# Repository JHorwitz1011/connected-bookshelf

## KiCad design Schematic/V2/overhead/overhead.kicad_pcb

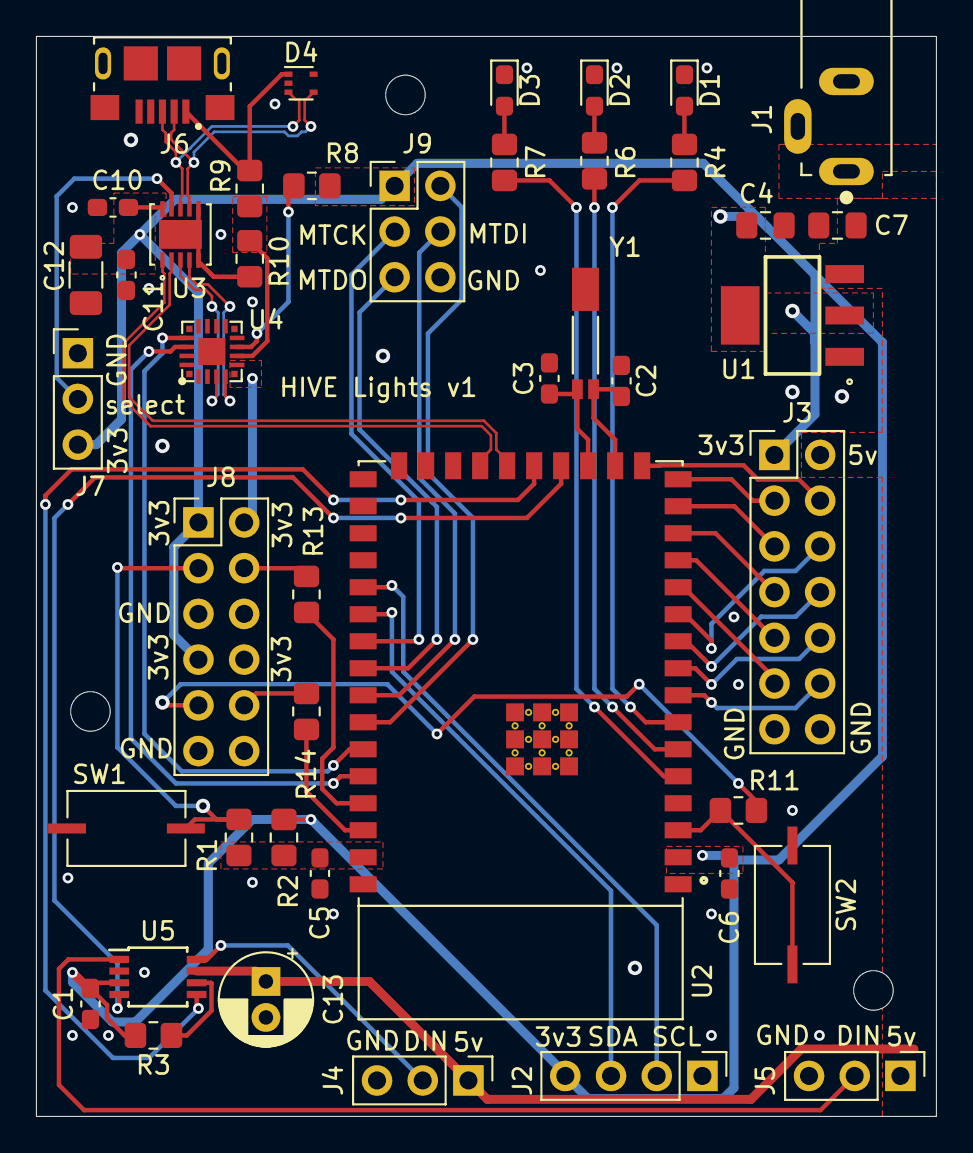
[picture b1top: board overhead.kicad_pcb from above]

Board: 2 copper layers, 50.0 x 60.0 mm, 44 parts (0 on the bottom side), 52 nets.

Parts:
C1, C6: 2.2 uF; C_0603_1608Metric_Pad1.08x0.95mm_HandSolder
C2, C3: 7 pF; C_0603_1608Metric_Pad1.08x0.95mm_HandSolder
C4, C7: 10 uF; C_0805_2012Metric_Pad1.18x1.45mm_HandSolder
C5: 0.1uF; C_0603_1608Metric_Pad1.08x0.95mm_HandSolder
C10, C11: 0.1 uF; C_0603_1608Metric_Pad1.08x0.95mm_HandSolder
C12: 4.7 uF; C_1206_3216Metric_Pad1.33x1.80mm_HandSolder
C13: 100 uF; CP_Radial_D5.0mm_P2.00mm
D1, D2, D3: LED; LED_0603_1608Metric_Pad1.05x0.95mm_HandSolder
D4: SP0503BAHTG; SOT-553
J1: PJ-031C; CUI_PJ-031C
J2: I2C; PinHeader_1x04_P2.54mm_Vertical
J3: GPIO; PinHeader_2x07_P2.54mm_Vertical
J4: Neopixel 1; PinHeader_1x03_P2.54mm_Vertical
J5: Neopixel 2; PinHeader_1x03_P2.54mm_Vertical
J6: 10118193-0001LF; FCI_10118193-0001LF
J7: Select Jumper; PinHeader_1x03_P2.54mm_Vertical
J8: STRAPPING; PinHeader_2x06_P2.54mm_Vertical
J9: JTAG; PinHeader_2x03_P2.54mm_Vertical
R1, R11, R13, R14: 470; R_0805_2012Metric_Pad1.20x1.40mm_HandSolder
R2, R3, R8: 10k; R_0805_2012Metric_Pad1.20x1.40mm_HandSolder
R4: 70; R_0805_2012Metric_Pad1.20x1.40mm_HandSolder
R6, R7: 65; R_0805_2012Metric_Pad1.20x1.40mm_HandSolder
R9: 22.1k; R_0805_2012Metric_Pad1.20x1.40mm_HandSolder
R10: 47.5k; R_0805_2012Metric_Pad1.20x1.40mm_HandSolder
SW1, SW2: SW_DIP_x01; PTS636 SM25F SMTR LFS
U1: NCP1117ST33T3G; SOT230P700X180-4N
U2: ESP32-S2-WROOM; XCVR_ESP32-S2-WROOM
U3: PI3USB221EZWEX
U4: CP2102N-A02-GQFN20R
U5: NTB0102; TSSOP-8_3x3mm_P0.65mm
Y1: MS3V-T1R; XTAL_MS3V-T1R

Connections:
+3V3: C1.1, C4.1, C6.2, C10.1, C11.1, C12.1, J2.4, J3.1, J7.3, J8.1, J8.2, J8.7, J8.8, J9.1, R2.1, R3.2, R8.1, U1.2, U1.4, U2.2, U3.10, U4.6, U4.7, U5.3
+5V: C7.2, C13.1, J1.1, J3.2, J4.1, J5.1, U1.3, U5.7
/RSTB: R8.2, U4.9
/VSens: R9.2, R10.1, U4.8
/XTAL_N: C3.1, U2.19, Y1.1
/XTAL_P: C2.1, U2.18, Y1.2
/select: J7.2, U3.9
BOOT: R11.1, SW2.1, U2.3
CHIP_PU: J8.3, R1.1, SW1.1
DIN1: J4.2, U5.8
DIN2: J5.2, U5.1
ESP32)D+: U2.23, U3.1
ESP32)D-: U2.22, U3.2
GLED: R6.1, U2.6
GND: C1.2, C2.2, C3.2, C4.2, C5.2, C6.1, C7.1, C10.2, C11.2, C12.2, C13.2, D1.1, D2.1, D3.1, D4.2, J1.2, J1.3, J2.1, J3.13, J3.14, J4.3, J5.3, J6.5, J6.S1, J6.S2, J6.S3, J6.S4, J6.S5, J6.S6, J7.1, J8.5, J8.6, J8.11, J8.12, J9.6, R10.2, SW1.2, SW2.2, U1.1, U2.1, U2.26, U2.42, U2.43, U3.5, U3.6, U3.11, U4.3, U4.12, U4.21, U5.2
IO5: J3.12, U2.8
IO6: J3.10, U2.9
IO7: J3.8, U2.10
IO8: J3.6, U2.11
IO9: J3.11, U2.12
IO10: J3.9, U2.13
IO11: J3.7, U2.14
IO12: J3.5, U2.15
IO13: J3.3, U2.16
IO14: J3.4, U2.17
IO37-SCL: J2.2, U2.31
IO38-SDA: J2.3, U2.32
IO45: R13.1, U2.39
IO46: R14.1, U2.40
MTCK: J9.3, U2.33
MTDI: J9.4, U2.35
MTDO: J9.5, U2.34
MTMS: J9.2, U2.36
Neopixel1: U2.21, U5.5
Neopixel2: U2.20, U5.4
unnamed: C5.1, R1.2, R2.2, U2.41
unnamed: D1.2, R4.2
unnamed: D2.2, R6.2
unnamed: D3.2, R7.2
unnamed: J8.4, R13.2
unnamed: J8.9, R11.2
unnamed: J8.10, R14.2
unnamed: R3.1, U5.6
RLED: R4.1, U2.7
RX0: U2.37, U4.17
TX0: U2.38, U4.18
UART)D+: U3.3, U4.4
UART)D-: U3.4, U4.5
USB)D+: D4.3, J6.3, U3.8
USB)D-: D4.4, J6.2, U3.7
VBUS: D4.1, J6.1, R9.1
YLED: R7.1, U2.5

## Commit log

2021-05-12 origanized repo
2021-05-12 initial server commit
2021-05-12 google api testing
2021-05-12 google api quickstart
2021-05-12 aws and tasks api integration
2021-05-12 bugfixing
2021-05-12 full integration test 1
2021-05-12 integration bug fixes
2021-05-12 integration color changes
2022-01-31 interim report
2022-01-31 added schematic
2022-04-24 uploaded code

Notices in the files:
parts and their libraries:
Copyright 2021 Accelerated Designs. All rights reserved.
